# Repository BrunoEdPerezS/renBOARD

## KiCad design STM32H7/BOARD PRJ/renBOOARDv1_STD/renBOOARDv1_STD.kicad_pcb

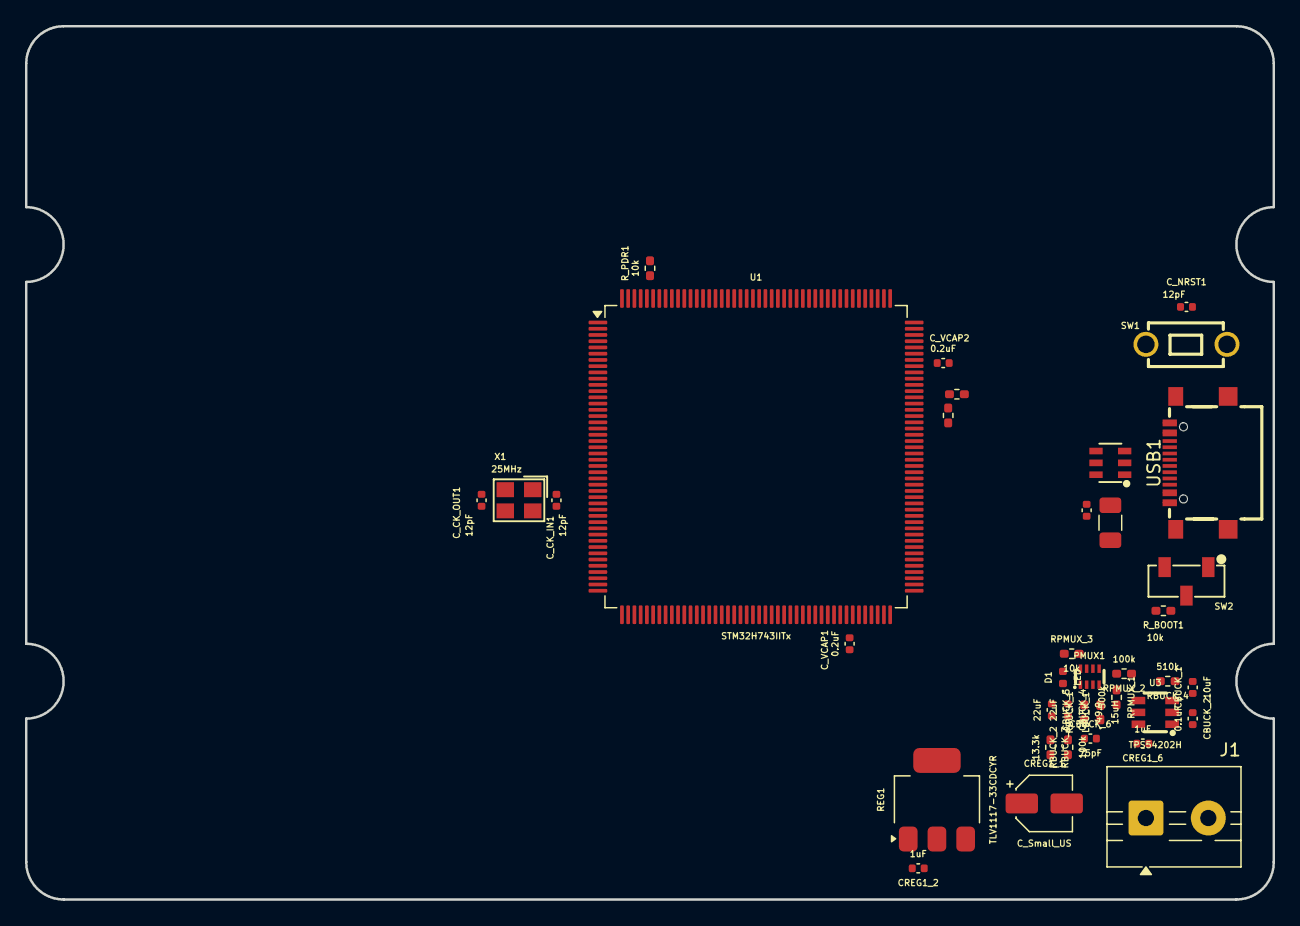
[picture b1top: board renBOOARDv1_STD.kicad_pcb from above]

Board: 2 copper layers, 100.0 x 70.0 mm, 38 parts (0 on the bottom side), 28 nets, no tracks yet.

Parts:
CBUCK_1: 10uF; C_0402_1005Metric
CBUCK_2: 0.1uF; C_0402_1005Metric
CBUCK_4, CBUCK_5: 22uF; C_0402_1005Metric
CBUCK_6: 75pF; C_0402_1005Metric
CREG1_1: C_Small_US; CP_Elec_4x5.3
CREG1_2, CREG1_6: 1uF; C_0402_1005Metric
C_CK_IN1, C_CK_IN2: 12pF; C_0402_1005Metric
C_CK_OUT1: 12pF; C_0402_1005Metric
C_NRST1: 12pF; C_0402_1005Metric
C_VCAP1, C_VCAP2: 0.2uF; C_0402_1005Metric
D1: LED; D_0402_1005Metric
F1: Fuse; Fuse_1206_3216Metric
J1: Screw_Terminal_01x02; TerminalBlock_MaiXu_MX126-5.0-02P_1x02_P5.00mm
LBUCK_1: 15uH; D_0402_1005Metric_Pad0.77x0.64mm_HandSolder
PMUX1: SOT-583-8_L2.1-W1.2-P0.50-LS1.6-BL
RBUCK_1: 49.9; R_0402_1005Metric_Pad0.72x0.64mm_HandSolder
RBUCK_2: 100k; R_0402_1005Metric_Pad0.72x0.64mm_HandSolder
RBUCK_3: 13.3k; R_0402_1005Metric_Pad0.72x0.64mm_HandSolder
RBUCK_4: 510k; R_0402_1005Metric_Pad0.72x0.64mm_HandSolder
RCC3, RCC4: 5.1k; R_0402_1005Metric_Pad0.72x0.64mm_HandSolder
REG1: TLV1117-33CDCYR; SOT-223
RPMUX_1: 500k; R_0402_1005Metric_Pad0.72x0.64mm_HandSolder
RPMUX_2: 100k; R_0402_1005Metric_Pad0.72x0.64mm_HandSolder
RPMUX_3: 10k; R_0402_1005Metric_Pad0.72x0.64mm_HandSolder
R_BOOT1: 10k; R_0402_1005Metric_Pad0.72x0.64mm_HandSolder
R_PDR1: 10k; R_0402_1005Metric_Pad0.72x0.64mm_HandSolder
SW1: SW-TH_L6.0-W3.5-P6.50
SW2: SW-SMD_CJS-1201A
TVS1: SOT-23-6_L2.9-W1.6-P0.95-LS2.8-BL
U1: STM32H743IITx; LQFP-176_24x24mm_P0.5mm
U3: TPS54202H; SOT-23-6_L2.9-W1.6-P0.95-LS2.8-BR
USB1: USB-SMD_USB-TYPE-C-020
X1: 25MHz; CRYSTAL-SMD_4P-L3.2-W2.5-BL

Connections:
+3.3V: CREG1_2.1, REG1.2 (VO), R_PDR1.1, SW2.1
+5V: CREG1_1.1, PMUX1.2 (VOUT), PMUX1.7 (VOUT), REG1.3 (VI)
+9V: CBUCK_1.1, CBUCK_2.1, J1.2, RBUCK_4.1, U3.3 (VIN)
/5V_BUCK: CBUCK_4.1, CBUCK_5.1, LBUCK_1.2, PMUX1.3 (VIN1), PMUX1.5 (MODE), RBUCK_1.2, RPMUX_1.2, RPMUX_3.2
/BOOT: R_BOOT1.1, U1.166 (BOOT0)
/BOOT_BUCK: CREG1_6.2, U3.6 (BOOT)
/D+: TVS1.1, USB1.A6 (Dp1), USB1.B6 (Dp2)
/D-: TVS1.3, USB1.A7 (Dn1), USB1.B7 (Dn2)
/EN_BUCK: RBUCK_4.2, U3.5 (EN)
/FB_BUCK: CBUCK_6.2, RBUCK_2.1, RBUCK_3.2, U3.4 (FB)
/NRST: C_NRST1.1, SW1.1, U1.31 (NRST)
/OSC_IN: C_CK_IN1.1, U1.29 (PH0), X1.1 (OSC1)
/OSC_OUT: C_CK_OUT1.1, U1.30 (PH1), X1.3 (OSC2)
/PDR: R_PDR1.2, U1.171 (PDR_ON)
/PMUX_PR1: PMUX1.4 (PR1), RPMUX_1.1, RPMUX_2.2
/PMUX_ST: D1.1 (K), PMUX1.8 (ST)
/SW_BUCK: CREG1_6.1, LBUCK_1.1, U3.2 (SW)
/USB_OTG_FS_D+: TVS1.6, U1.123 (PA12)
/USB_OTG_FS_D-: TVS1.4, U1.122 (PA11)
/USB_OTG_FS_VSBUS: RCC3.2, RCC4.1, U1.120 (PA9)
/VBUS_SIG: C_CK_IN2.1, F1.1, RCC3.1, TVS1.5, USB1.A4 (VBUS), USB1.A9 (VBUS), USB1.B4 (VBUS), USB1.B9 (VBUS)
/VCAP1: C_VCAP1.1, U1.81 (VCAP)
/VCAP2: C_VCAP2.1, U1.125 (VCAP)
GND: CBUCK_1.2, CBUCK_2.2, CBUCK_4.2, CBUCK_5.2, CREG1_1.2, CREG1_2.2, C_CK_IN1.2, C_CK_IN2.2, C_CK_OUT1.2, C_NRST1.2, C_VCAP1.2, C_VCAP2.2, J1.1, PMUX1.1 (GND), RBUCK_3.1, RCC4.2, REG1.1 (GND), RPMUX_2.1, SW1.2, SW2.3, TVS1.2, U1.14 (VSS), U1.22 (VSS), U1.37 (VSSA), U1.48 (VSS), U1.61 (VSS), U1.71 (VSS), U1.90 (VSS), U1.102 (VSS), U1.113 (VSS), U1.126 (VSS), U1.135 (VSS), U1.148 (VSS), U1.158 (VSS), U3.1 (GND), USB1.A1 (GND), USB1.A12 (GND), USB1.B1 (GND), USB1.B12 (GND), X1.2 (GND), X1.4 (GND)
unnamed: CBUCK_6.1, RBUCK_1.1, RBUCK_2.2
unnamed: D1.2 (A), RPMUX_3.1
unnamed: R_BOOT1.2, SW2.2 (C)
VBUS: F1.2, PMUX1.6 (VIN2)

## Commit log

2025-09-07 BASICS
2025-09-13 Se ha creado el PWDN
2025-09-15 Avance en USB
